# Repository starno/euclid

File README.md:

euclid
=====

Low Cost, High Performance, Delta Robot framework

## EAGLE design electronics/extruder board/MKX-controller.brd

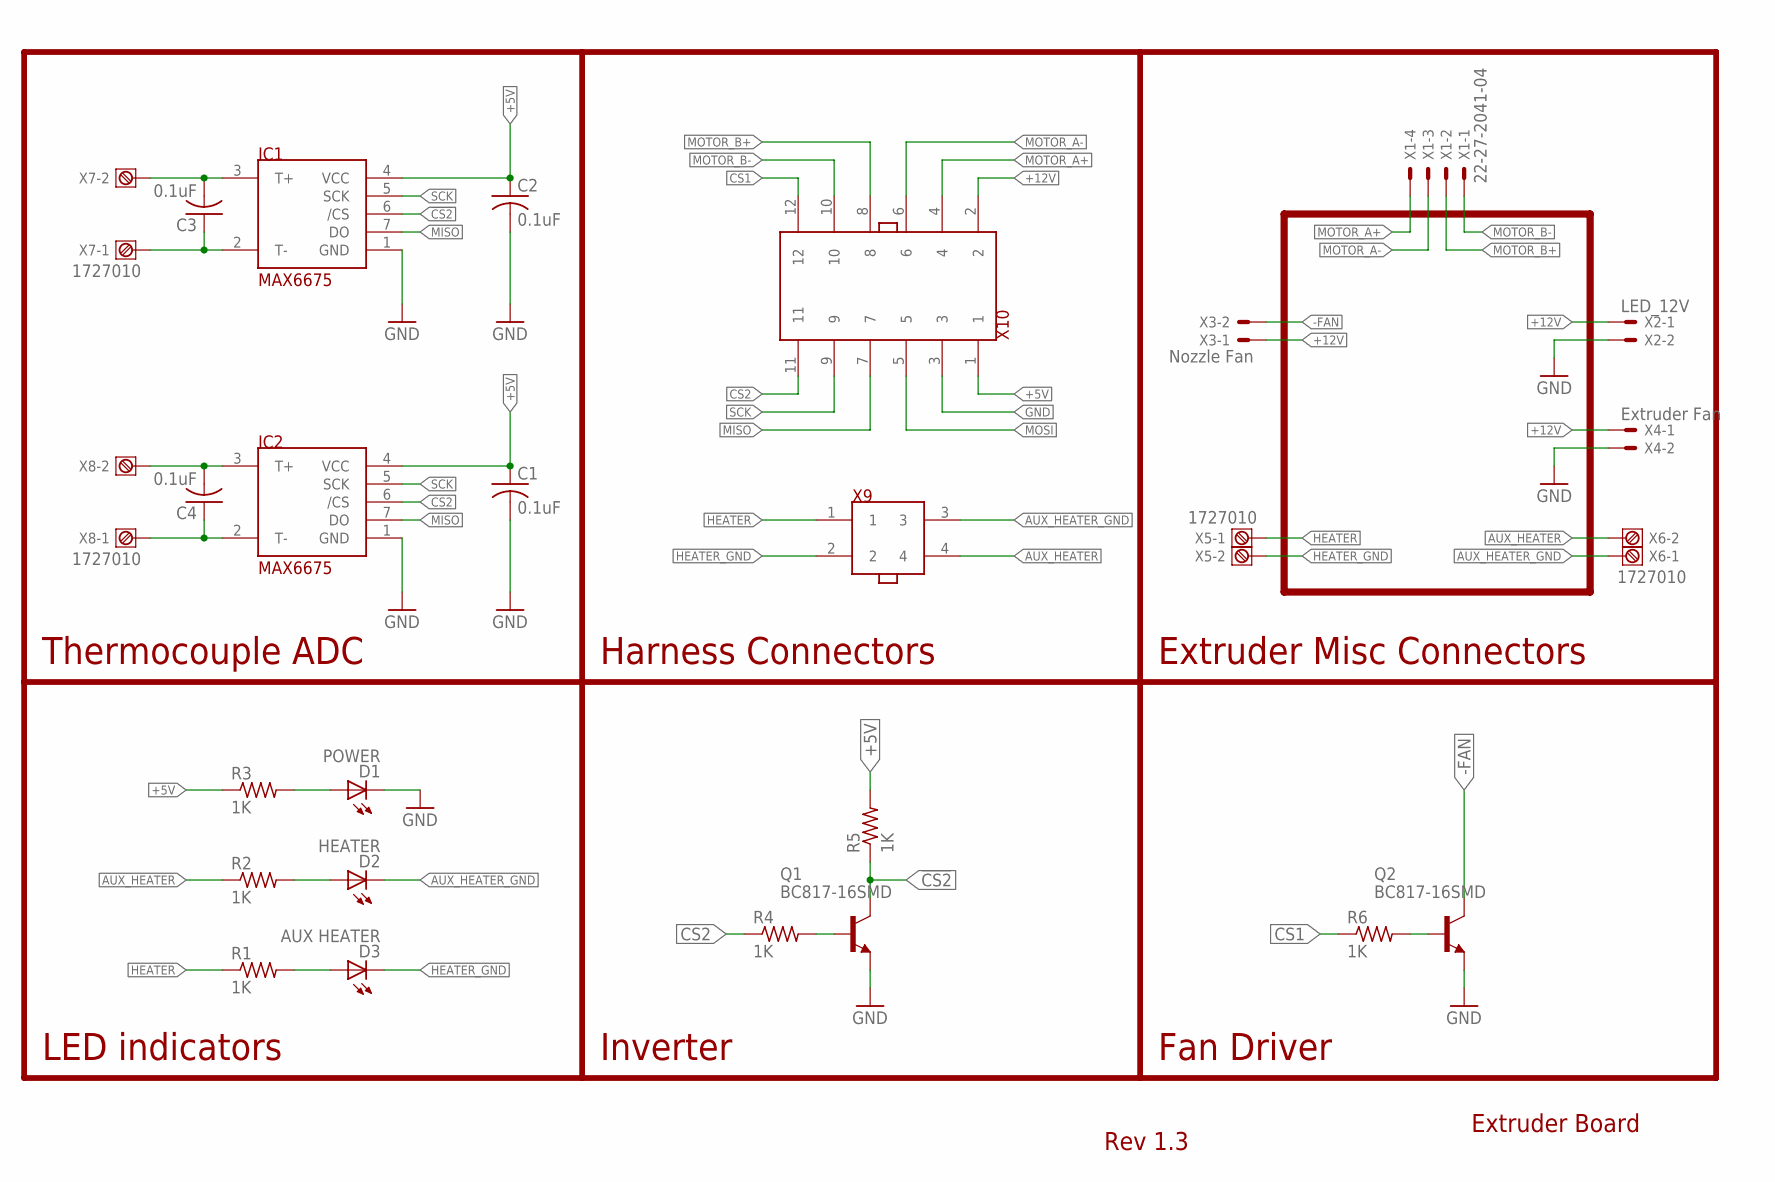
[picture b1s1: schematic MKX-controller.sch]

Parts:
C1, C2, C3, C4: 0.1uF; C0603K
D1: POWER; CHIPLED_0805
D2: HEATER; CHIPLED_0805
D3: AUX HEATER; CHIPLED_0805
IC1, IC2: MAX6675; SO-8
Q1, Q2: BC817-16SMD; SOT23-BEC
R1, R2, R3, R4, R5, R6: 1K; R0603
X1: 22-27-2041-04; 6410-04
X2: LED_12V; 6410-02
X3: Nozzle Fan; 6410-02
X4: Extruder Fan; 6410-02
X5, X6, X7, X8: 1727010
X9: 5557-04
X10: 5557-12

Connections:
!CS2: IC1.6 (/CS), Q1.C, R5.1
+5V: C1.1, C2.1, IC1.4 (VCC), IC2.4 (VCC), R3.1, R5.2, X10.1
+12V: X2.1, X3.1, X4.1, X10.2
-FAN: Q2.C, X3.2
AUX_HEATER: R2.1, X6.2, X9.4
AUX_HEATER_GND: D2.C, X6.1, X9.3
CS1: R6.1, X10.12
CS2: IC2.6 (/CS), R4.1, X10.11
GND: C1.2, C2.2, D1.C, IC1.1 (GND), IC2.1 (GND), Q1.E, Q2.E, X2.2, X4.2, X10.3
HEATER: R1.1, X5.1, X9.1
HEATER_GND: D3.C, X5.2, X9.2
MISO: IC1.7 (DO), IC2.7 (DO), X10.7
MOSI: X10.5
MOTOR_A+: X1.4, X10.4
MOTOR_A-: X1.3, X10.6
MOTOR_B+: X1.2, X10.8
MOTOR_B-: X1.1, X10.10
unnamed: C4.1, IC2.2 (T-), X8.1
unnamed: C3.1, IC1.2 (T-), X7.1
unnamed: C3.2, IC1.3 (T+), X7.2
unnamed: C4.2, IC2.3 (T+), X8.2
unnamed: D1.A, R3.2
unnamed: Q1.B, R4.2
unnamed: D2.A, R2.2
unnamed: D3.A, R1.2
unnamed: Q2.B, R6.2
SCK: IC1.5 (SCK), IC2.5 (SCK), X10.9

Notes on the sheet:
Harness Connectors
Extruder Misc Connectors
Thermocouple ADC
LED indicators
Inverter
Fan Driver
Extruder Board
Rev 1.3

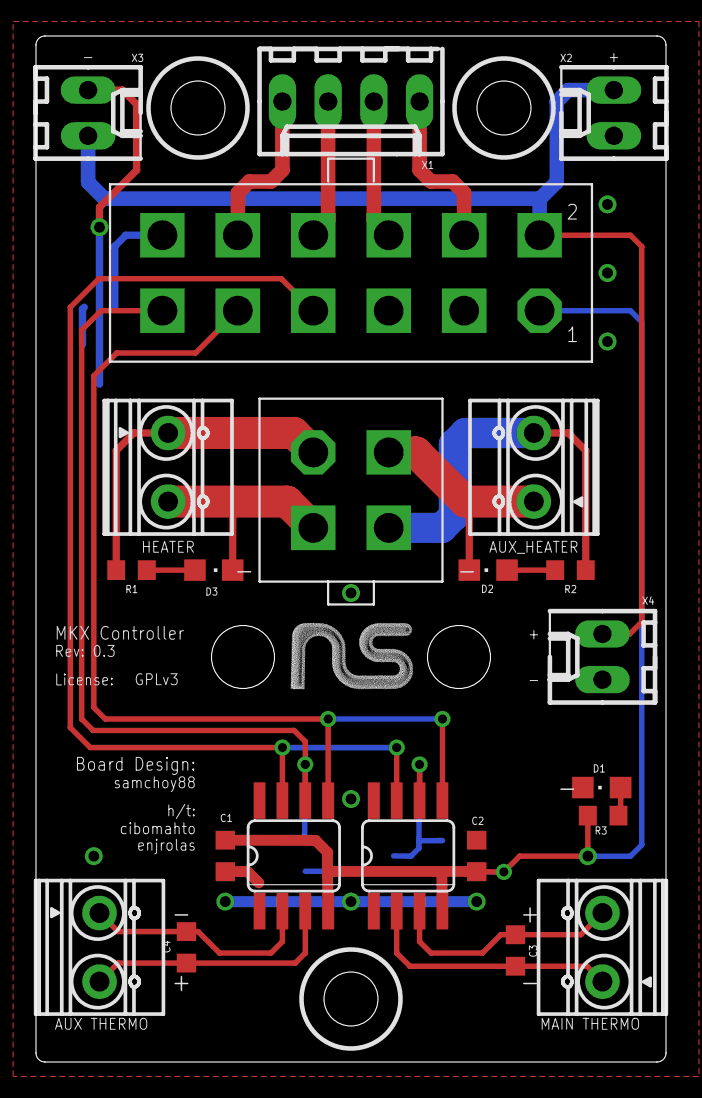
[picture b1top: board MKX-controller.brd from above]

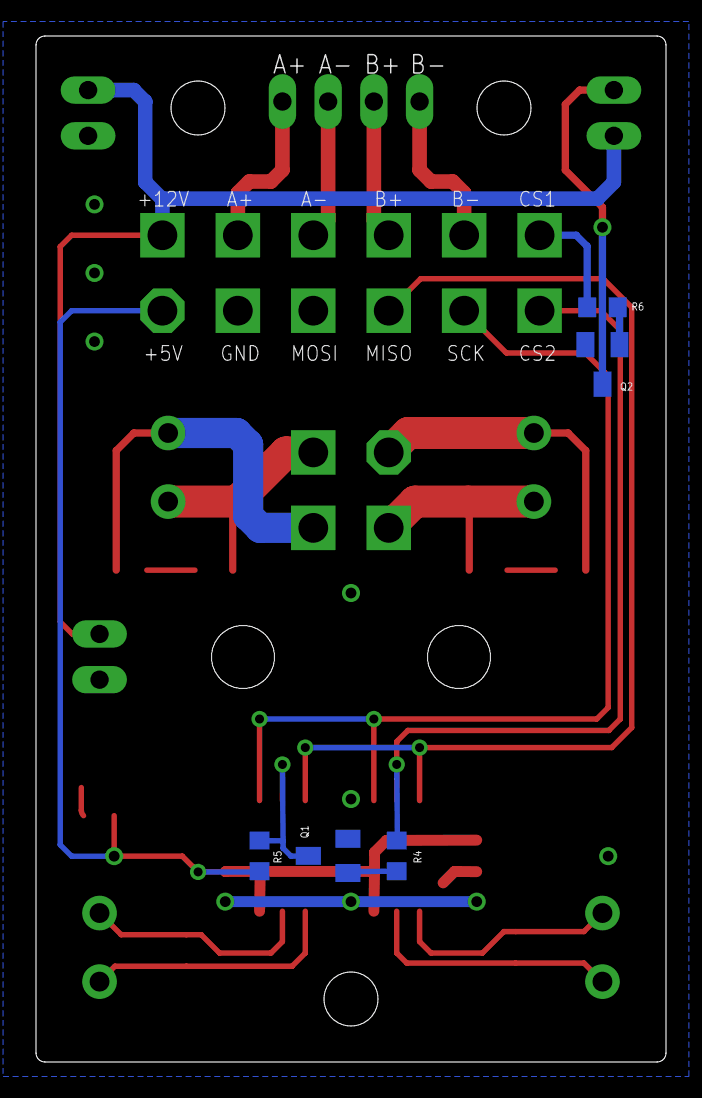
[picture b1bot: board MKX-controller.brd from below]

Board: 2 copper layers, 35.0 x 57.0 mm, 27 parts (5 on the bottom side), 26 nets.

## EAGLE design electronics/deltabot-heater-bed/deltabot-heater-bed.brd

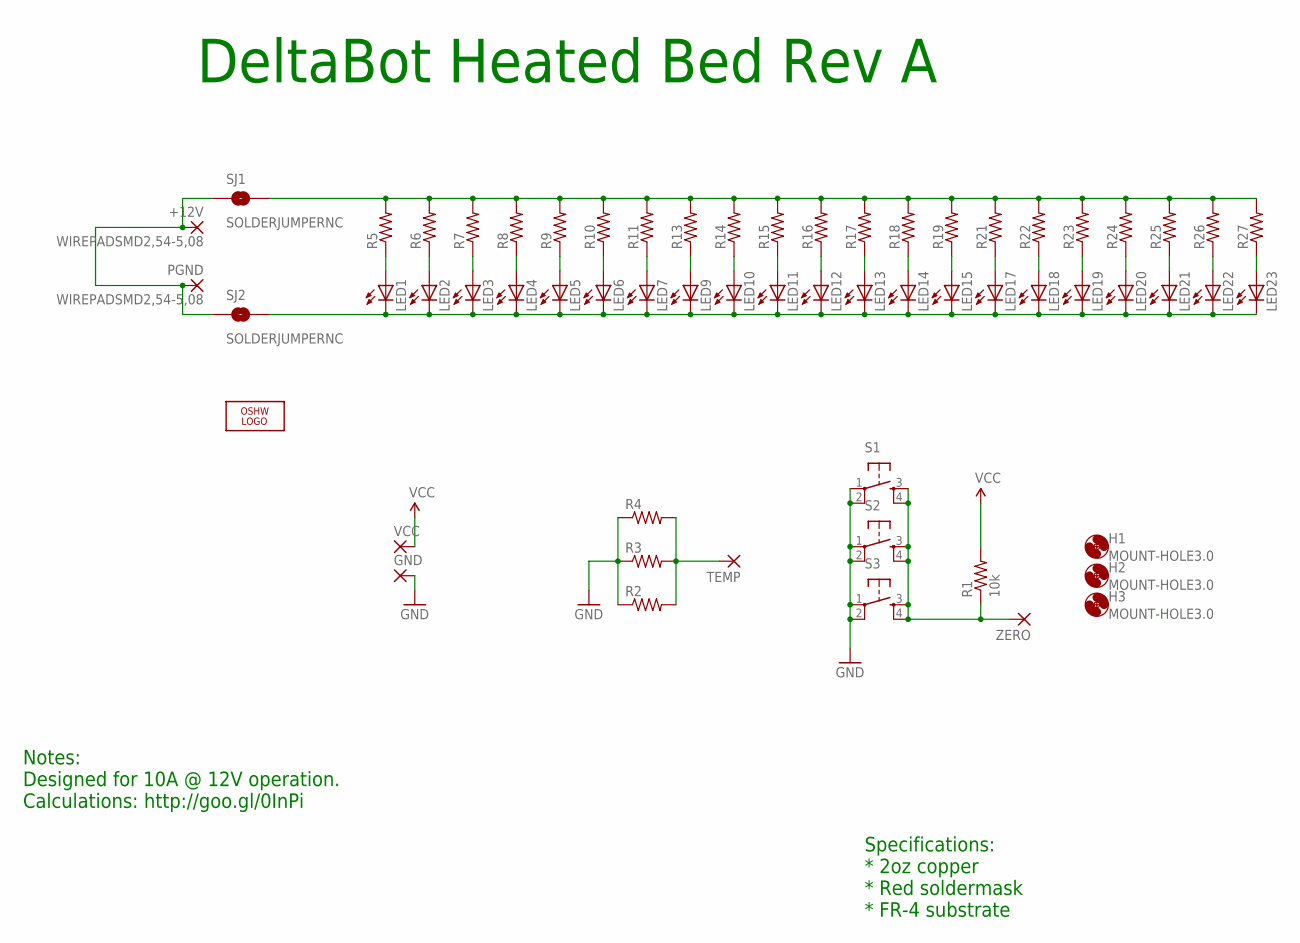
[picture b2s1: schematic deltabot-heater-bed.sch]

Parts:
+12V: WIREPADSMD2,54-5,08; SMD2,54-5,08
GND: SMD2; SMD1,27-2,54
H1, H2, H3: MOUNT-HOLE3.0; 3,0
LED1, LED2, LED3, LED4, LED5, LED6, LED7, LED9, LED10, LED11, LED12, LED13, LED14, LED15, LED17, LED18, LED19, LED20, LED21, LED22, LED23: LED0805; 0805-LED
LOGO1: OSHW_LOGO_FILLX1000-NT; OSHW_FILLX1000_NOTEXT
PGND: WIREPADSMD2,54-5,08; SMD2,54-5,08
R1: 10k; 0805-RC
R2: RESISTOR1206; 1206-RC
R3, R5, R6, R7, R8, R9, R10, R11, R13, R14, R15, R16, R17, R18, R19, R21, R22, R23, R24, R25, R26, R27: RESISTOR0805; 0805-RC
R4: RESISTOR0603; 0603-RC
S1, S2, S3: TAC_SWITCHSMD; TACTILE_SWITCH_SMD
SJ1, SJ2: SOLDERJUMPERNC; SJ_2S
TEMP: SMD2; SMD1,27-2,54
VCC: SMD2; SMD1,27-2,54
ZERO: SMD2; SMD1,27-2,54

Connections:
12V: R5.2, R6.2, R7.2, R8.2, R9.2, R10.2, R11.2, R13.2, R14.2, R15.2, R16.2, R17.2, R18.2, R19.2, R21.2, R22.2, R23.2, R24.2, R25.2, R26.2, R27.2, SJ1.2
GND: GND.1, R2.1, R3.1, R4.1, S1.1, S1.2, S2.1, S2.2, S3.1, S3.2
HEATER: +12V.1, PGND.1, SJ1.1, SJ2.1
unnamed: R2.2. (2), R3.2, R4.2, TEMP.1
unnamed: LED1.A, R5.1
unnamed: LED2.A, R6.1
unnamed: R1.1, S1.3, S1.4, S2.3, S2.4, S3.3, S3.4, ZERO.1
unnamed: LED3.A, R7.1
unnamed: LED4.A, R8.1
unnamed: LED5.A, R9.1
unnamed: LED6.A, R10.1
unnamed: LED7.A, R11.1
unnamed: LED9.A, R13.1
unnamed: LED10.A, R14.1
unnamed: LED11.A, R15.1
unnamed: LED12.A, R16.1
unnamed: LED13.A, R17.1
unnamed: LED14.A, R18.1
unnamed: LED15.A, R19.1
unnamed: LED17.A, R21.1
unnamed: LED18.A, R22.1
unnamed: LED19.A, R23.1
unnamed: LED20.A, R24.1
unnamed: LED21.A, R25.1
unnamed: LED22.A, R26.1
unnamed: LED23.A, R27.1
PGND: LED1.C, LED2.C, LED3.C, LED4.C, LED5.C, LED6.C, LED7.C, LED9.C, LED10.C, LED11.C, LED12.C, LED13.C, LED14.C, LED15.C, LED17.C, LED18.C, LED19.C, LED20.C, LED21.C, LED22.C, LED23.C, SJ2.2
VCC: R1.2, VCC.1

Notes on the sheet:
Specifications: * 2oz copper * Red soldermask * FR-4 substrate
DeltaBot Heated Bed Rev A
Notes: Designed for 10A @ 12V operation. Calculations: http://goo.gl/0InPi

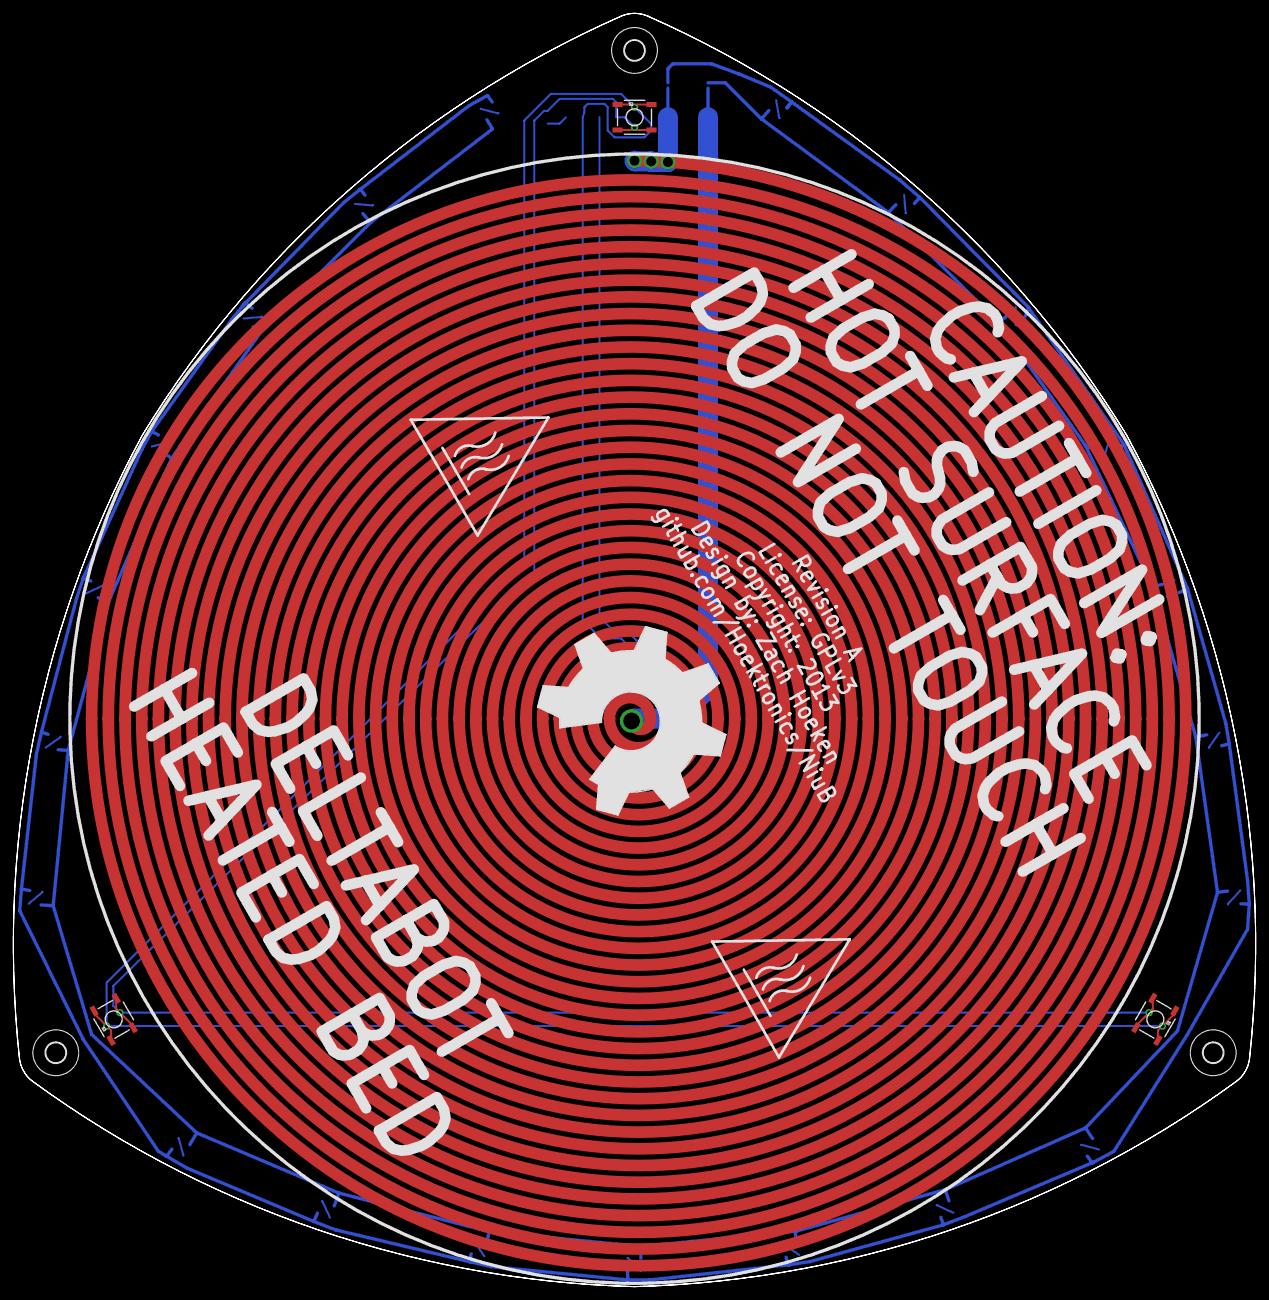
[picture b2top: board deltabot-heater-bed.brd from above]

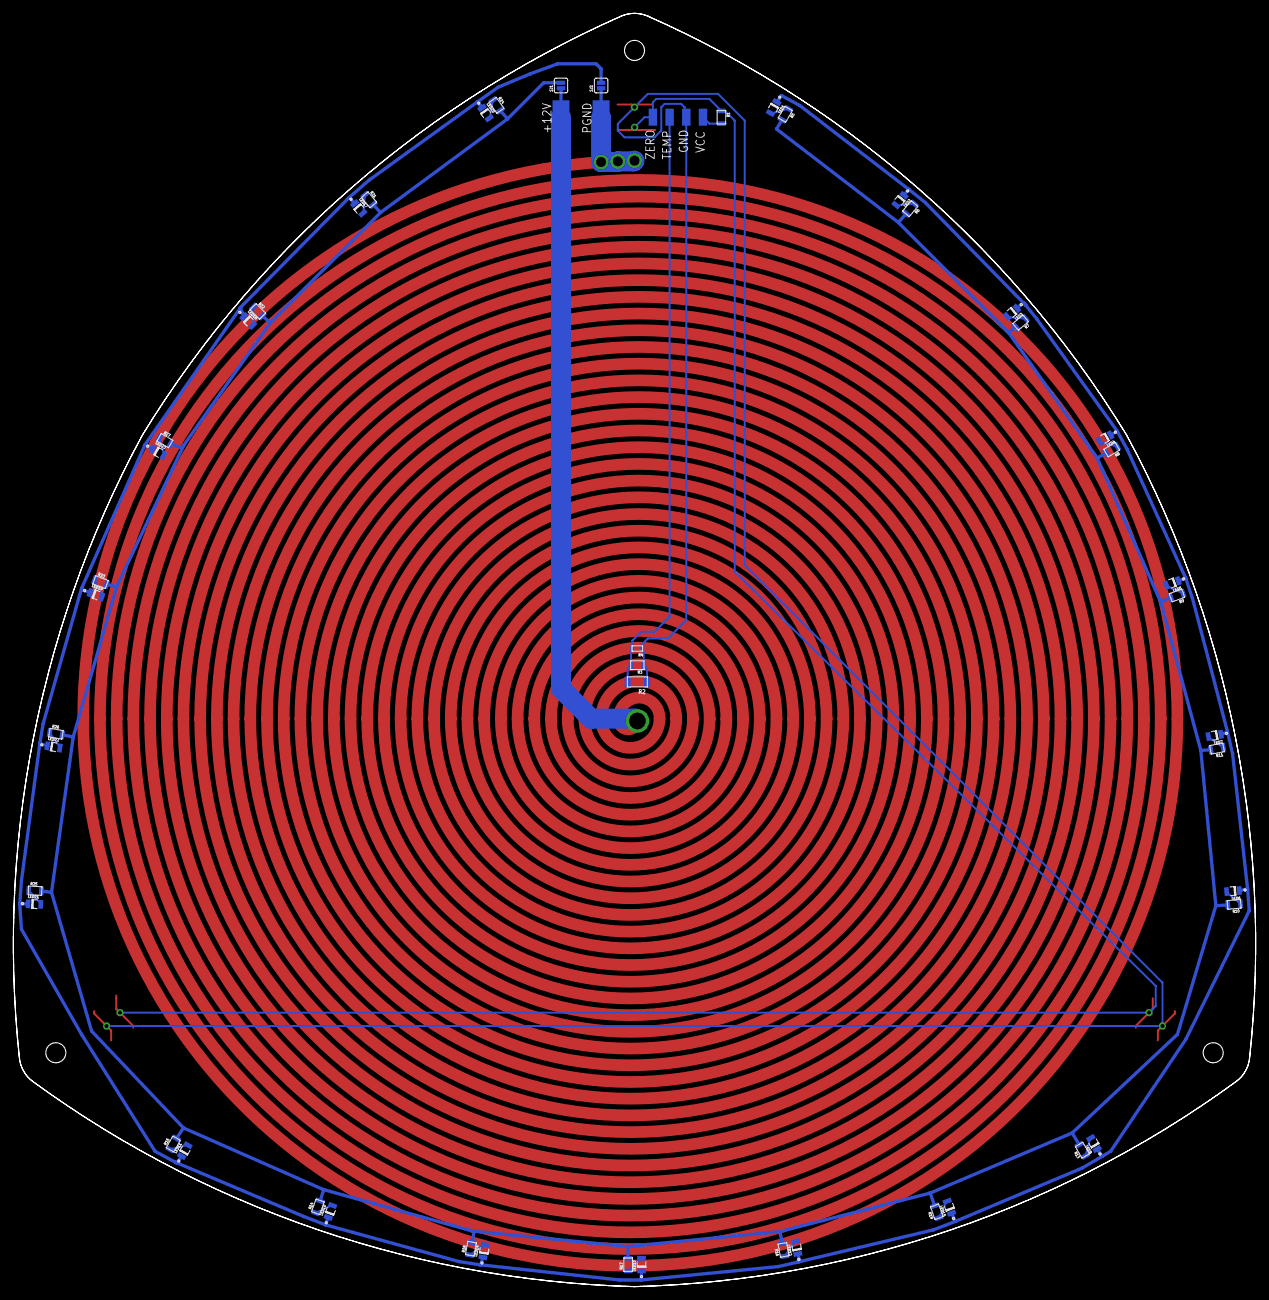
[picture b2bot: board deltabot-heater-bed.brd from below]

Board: 2 copper layers, 185.9 x 190.5 mm, 61 parts (54 on the bottom side), 28 nets.

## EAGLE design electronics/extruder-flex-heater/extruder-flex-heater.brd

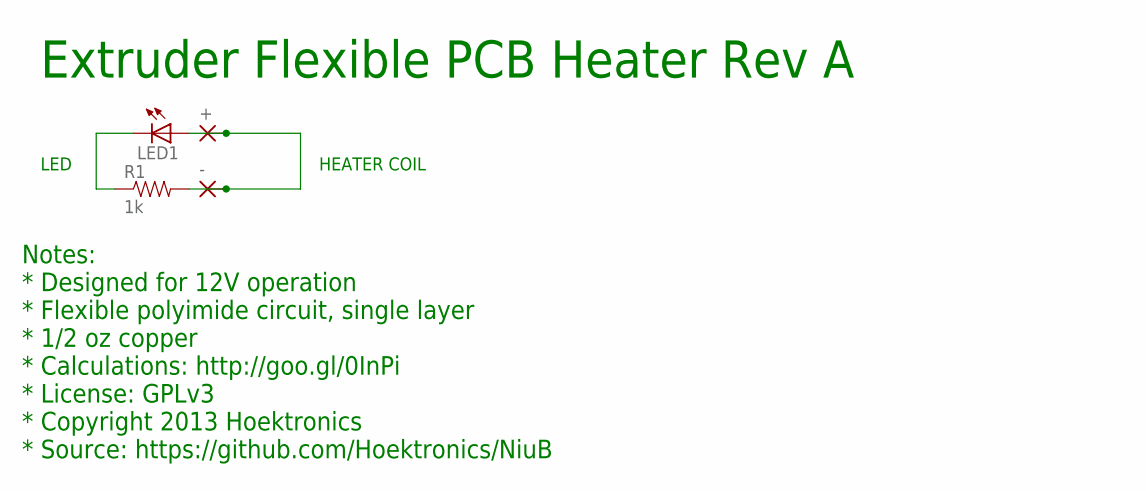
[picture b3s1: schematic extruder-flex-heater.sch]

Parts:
+: SMD2; SMD1,27-2,54
-: SMD2; SMD1,27-2,54
LED1: LED0805; 0805-LED
R1: 1k; 0805-RC

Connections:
HEATER: +.1, -.1, LED1.A, R1.2
unnamed: LED1.C, R1.1

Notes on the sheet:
HEATER COIL
LED
Notes: * Designed for 12V operation * Flexible polyimide circuit, single layer * 1/2 oz copper * Calculations: http://goo.gl/0InPi * License: GPLv3 * Copyright 2013 Hoektronics * Source: https://github.com/Hoektronics/NiuB
Extruder Flexible PCB Heater Rev A

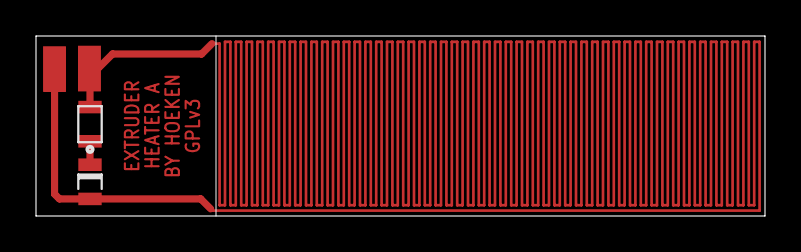
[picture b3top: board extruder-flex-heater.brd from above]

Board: 2 copper layers, 40.5 x 10.0 mm, 4 parts (0 on the bottom side), 2 nets.

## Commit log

2012-08-25 first commit. added list of machine variables
2012-08-25 started Solidworks modeling
2012-08-25 Added Niubi logo in readme
2012-08-25 whoops, sorted out a mess
2012-08-25 now it's clean
2012-08-25 this is annoying
2012-08-27 Added rod end joints and cleaned up order of operations
2012-09-05 Added bearing clamps and carriage into master file
2012-09-13 added a couple rough drafts into the master of some motor mounting conepts
2012-09-13 created a machine configuration file for easier parameter control
2012-09-13 Added nuibi SLDPRT as a fresh approach at maintaining a fully parametric model
2012-09-13 started on sheetmetal for main axis assembly
2012-09-14 Added pulley and cleaned up some equations
2012-09-14 Revert "Added nuibi SLDPRT as a fresh approach at maintaining a fully parametric model"
    This reverts commit 5260621ced5dce17bcdd80928afb1bb89083fd7d.
2012-09-14 started on rod clamps
2012-09-15 cleaned up some relations
2013-04-12 Deleted useless files
2013-04-12 frame and base master files along with subparts
2013-04-12 added axis master and sub-components
2013-04-12 Deleted variables.txt, useless placeholder
2013-04-12 ignore weird file
2013-04-12 changed some part names for consistency
2013-04-13 added door, hinge, and mounting array
2013-04-13 added window bracket single mount
2013-04-25 Added Bottom assembly
2013-04-25 Added door handle to door master
2013-04-25 added handle mounting holes
2013-04-25 Added base assembly
2013-04-25 deleted Stock-Frame master-1 mysterious file
2013-04-25 added electronics mounting and support holes to base
2013-04-25 Added PSU
2013-04-25 added PSU to base assembly
2013-04-25 added axis master and parts
2013-04-25 converted wall into sheet metal part
2013-04-25 created axis assembly
2013-04-25 created axis idler assembly
2013-04-25 extended sk10 seperation distance for long carriage
2013-04-25 included idler bracket assembly into axis assembly
2013-04-25 created top assembly
2013-05-13 2013 conversion, added more electronics plate support, extended rod length to 400mm
2013-05-13 cleaned up windows and bay layout
2013-05-13 updated bottom assembly
2013-05-13 created stacked window bracket
2013-05-13 added stacked brackets to base assembly
2013-05-26 updated idler bracket subassembly mates
2013-05-26 added lasercut production layout
2013-05-26 top assembly parts updated to 2013
2013-05-26 Added arduino to base assembly
2013-05-29 Added bottom crenelations to frame master, pscover and baseplate
2013-05-29 added chamfers to base crenelations
2013-05-29 added chamfers to bottom crenelations
2013-05-29 added powerswitch and USB mounts to switch cover
2013-05-29 added exhaust grill to bay cover
2013-05-29 added Brain sub-assembly
2013-05-29 added grill and shortened windows
2013-05-29 trimmed down door, adding clearance
2013-05-29 added fan and guard mounting to switch cover
2013-05-29 rough assembly
2013-05-29 lasercut layout updated
2013-06-09 removed old base support holes
2013-06-09 removed old mains switch mounting holes on base
2013-06-09 moved arduino mount over by 12mm to avoid motor interference
2013-06-09 fixed arduino mounting hole spacing from mirroring error
2013-06-09 moved usb access on acrylic switch cover 12mm to line up with new arduino placement
2013-06-09 moved acrylic switch cover fan mount by 12mm
2013-06-09 moved arduino closer to acrylic face for easier USB access
2013-06-09 suppress sheet metal features on bent wall
2013-06-10 made nut pockets stronger on window brackets
2013-06-10 added L-bracket mounting for windows, central reinforcment holes with wall
2013-06-10 removed extra mounting holes in base for window bracket arrangement
2013-06-10 removed window-bracket-stack as a part and from assemblies
2013-06-10 revised base assembly so only hole blocked by arduino removed
2013-06-10 added window brackets to base/brain assembly
2013-06-10 revised motor bracket nut-pockets to match window brackets
2013-06-11 added motors to axis subassembly
2013-06-11 updated RAMPS CAD to more accurate model
2013-06-11 removed old RAMPS directory and files
2013-06-11 improved arduino mounting holes, pushed it back from window face
2013-06-12 Added magnet bracket to door, improved handle
2013-06-12 improved handle for easier printing
2013-06-12 made door latch clearance around magnets a little tighter
2013-06-25 updated lasercut layout assembly and added drawing for easy dxf export
2013-06-25 added motor brackets plate and printing plate directory
2013-06-25 renamed motor bracket plate
2013-06-25 added clamps printing plate
2013-06-25 added idler bracket printing plate assembly
2013-06-25 added window bracket printing plate assembly
2013-06-25 put lasercut assembly into new folder
2013-06-27 added slots to door for hinge adjustment
2013-06-27 updated lasercut assembly and drawing for door adjustments
2013-06-27 added belt to axis-idler-assembly
2013-06-27 updated axis assembly
2013-06-27 added in fanguard and fan into bottom assembly
2013-07-15 added electronics folder with heater boards and release script.
2013-07-15 board is ready for rev a release.
2013-07-15 updated eagle release script.
2013-07-15 i think its ready for a release. added docs and a frame.
2013-07-16 heater boards ready for release.
2013-07-16 tweaked the traced width a bit.
2013-07-22 added delta platform mounting holes to frame master
2013-07-22 added leveling bracket holes to base master
2013-07-23 moved arduino placement from outer wall
2013-07-23 added Raspi mounting and slots for delta PCB routing
2013-07-23 added camera mount
2013-07-23 Added mounting hole to base master now that arduino is not in the way
2013-07-23 fixed the camera mount hole spacing.
2013-07-23 updated lasercut layout assembly and drawing
2013-07-23 moved camera and mount to parts>extras
2013-07-24 changed USB and Ethernet extension cable mounting
2013-07-24 added power switch
2013-07-24 added raspberry pi board to base assembly
2013-07-24 added usb b2b extension cable
2013-07-24 added ethernet extension cable
2013-07-24 adjusted switch spacing
2013-07-26 Updated camera mount viewing angle
2013-07-26 added heat sheild to base assembly
2013-07-26 added standoffs, heat shield and extra window bracket to base assembly
2013-07-26 updated to delta platform in base assembly
2013-07-26 added contsraints to base assembly
2013-07-26 base assembly edits
2013-07-26 updated base assembly parts
2013-07-28 added rubber feet
2013-07-29 stuff
2013-07-29 fixed extension cable placement to get fan further back. added additional venting in bay cover
2013-08-07 fixed extension cable mounting in bottom-assembly
2013-08-08 added updated end effector files
2013-08-08 added carbon tubes and arm standoffs
2013-08-08 added arm assemblies
2013-08-25 added extrudate fans
2013-08-25 added door handle and extrudate fans to extras-plate
2013-09-01 added python calibration scripts
2013-09-04 added list for delta platform rev2
2013-09-11 added screen printing illustrator and BMP files for heatbed
2013-09-24 updated extras-plate
2013-09-24 added carriage assembly
2013-09-24 added carriage printing plate assembly
2013-09-25 changed linear bearing to LM10LUU, updated carriage assembly
2013-09-25 added magnet features to idler bracket
2013-09-25 added endstop and magnets to axis idler assembly
2013-09-27 updated end effector assembly
2013-09-27 deleted old arm assembly
2013-09-27 updated carbon fiber length, arm assembly
2013-09-29 added extruder board
2013-09-30 nothing important
2013-09-30 added arm spring clip
2013-09-30 added spring clips to arm assembly
2013-09-30 updated arm separation distance
2013-09-30 updated pscover
2013-11-06 changed axis idler config
2013-12-13 trashed old gerber files
2013-12-13 extruder board rev1
2013-12-14 Updated extruder board V1.1
    -Changed pin assignment on connectors
    -fixed bugs on Left / Right Fan
2013-12-14 Revert "Updated extruder board V1.1"
    This reverts commit 2d423195ed33dd4a98d803fb0bad6f27ea0b4d36.
2013-12-15 Moved filament entry back 20mm from center on acrylic-top to better suit piral harness
2013-12-15 made NS logo perimeter only with no fill
2013-12-15 added euclid logo to carriage
2013-12-15 changed carriage offset to 23mm from 25 for strength, added support to backside of standoff for less slop at higher speeds
2013-12-15 Altered carriage printing assembly to fit more parts all in same build
2013-12-15 improved window-bracket-plate printing assembly for effeciency
2013-12-15 removed idler-bracket-magnet, updated idler bracket file
2013-12-15 Changed idler magnet from 4mm thick to 5mm
2013-12-15 Updated axis assemblies and relations
2013-12-15 one more file
2013-12-23 Revert "Revert "Updated extruder board V1.1""
    This reverts commit 95d31b6e42416120fe44263da72c55e619acdaa4.
2013-12-23 Clean up repository
2014-02-23 Extruder board V1.2
    -Changed harness pin assignment
    -Added nozzle fan driver and using pin CS1 as control signal
    -Added invert circuit and using pin CS2 to control both thermocouple ADC
    -Isolated the AUX heater GND and Heater GND
2014-03-06 githalytics
2014-03-10 Extruder board V1.3
    1. remove the T style cutouts in the front
    2. Added holes for filament insert
    3. extended board size
2014-03-11 fixed typo, added attribution on silkscreen
2014-03-11 added bmp logo, changed filament hole size to 3.5mm
2014-03-11 renamed all old extruder controller board files
2014-05-06 updated HBP files
2014-05-06 deleted some extra files
2014-05-07 Fixed HBP outline width for gerber export
2014-09-10 added new end effector master file
2014-09-10 added new end effector to the parts directory
2014-09-10 removed broken external references in the end effector assembly
2014-09-10 deleted old end effector parts
2014-09-10 fixed all external broken references on endeffector assembly
2014-09-10 fixed interference with wedge on carriage
2014-09-11 fixed motherfucking external reference and equation errors in carriage master file
2014-09-11 updated carriage 3dprinting plate assembly
2014-09-11 Fixed resulting errors in the axis assembly
2014-09-11 Fixed all reference errors in part assemblies
2014-09-11 deleted duplicate standoff
2014-09-15 updated url on faceplate
2014-09-15 removed square HBP mounting holes
2014-09-15 fixed broken mates in Idler bracket printing assembly
2014-09-15 created end effector printing plate assembly
2014-09-15 added end effector printing plate STL and readme
2014-09-16 deleted clamps plate assembly (no longer needed)
2014-09-16 updated all printing assemblies to sit on front plane for easier STL export
2014-09-16 added all printing STLs with recommended print settings in their respective READMEs
2014-09-18 exported Lasercut frame
2014-09-23 Added lasercut files for 600mmx400mm sheets
2014-09-23 added lasercut files for 900mmx600mm sheets
2014-09-23 Added lasercut files for full sheets
2014-09-23 deleted duplicate file
2014-10-01 added lasercut production files for the tower bending fixture

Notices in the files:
parts and their libraries:
SparkFun-Electromechanical: Licensing: CC v3.0 Share-Alike You are welcome to use this library for commercial purposes.
